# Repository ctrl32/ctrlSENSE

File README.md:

# ctrlSENSE

Open-source IoT temperature sensors – firmware, hardware and server in one repository.

## Repository layout

| Directory | Content | License |
|---|---|---|
| [`firmware/`](firmware/) | Sensor firmware (ESP32, PlatformIO) | GPL-3.0-or-later |
| [`hardware/`](hardware/) | PCB (KiCad) and enclosure (FreeCAD) | CERN-OHL-S-2.0 |
| [`server/`](server/) | Backend and dashboard | AGPL-3.0-or-later |
| [`docs/`](docs/) | Documentation | CC-BY-SA-4.0 |

## Getting started

### Firmware

```bash
cd firmware
pio run                 # build
pio run -t upload       # flash
pio device monitor      # serial monitor
```

Requires [PlatformIO](https://platformio.org/).

### Hardware

Open `hardware/pcb/` in [KiCad](https://www.kicad.org/) 9 and `hardware/enclosure/` in [FreeCAD](https://www.freecad.org/) 1.0 or newer.

## Contributing

Contributions are welcome – see [CONTRIBUTING.md](CONTRIBUTING.md).
Security issues: see [SECURITY.md](SECURITY.md).

## License

ctrlSENSE uses different licenses for different parts of the project – see [LICENSE](LICENSE).
All parts are under strong copyleft licenses: if you distribute modified versions
(or, for the server, run them as a network service), you must publish the
source under the same license.
The ctrlSENSE name and logo are covered by [TRADEMARKS.md](TRADEMARKS.md).

© 2026 ctrl32

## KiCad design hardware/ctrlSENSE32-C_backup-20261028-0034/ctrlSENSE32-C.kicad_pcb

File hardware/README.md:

# ctrlSENSE hardware

| Directory | Content | Tool |
|---|---|---|
| [`pcb/`](pcb/) | Schematic and PCB | KiCad 9 |
| [`enclosure/`](enclosure/) | Enclosure | FreeCAD 1.0+ |

Manufacturing files (Gerber, drill, BOM, pick-and-place) are attached to
[releases](https://github.com/ctrl32/ctrlSENSE/releases) and are not stored in
the repository.

Licensed under [CERN-OHL-S-2.0](../LICENSES/CERN-OHL-S-2.0.txt).
If you distribute a modified design, you must publish its source under the
same license.

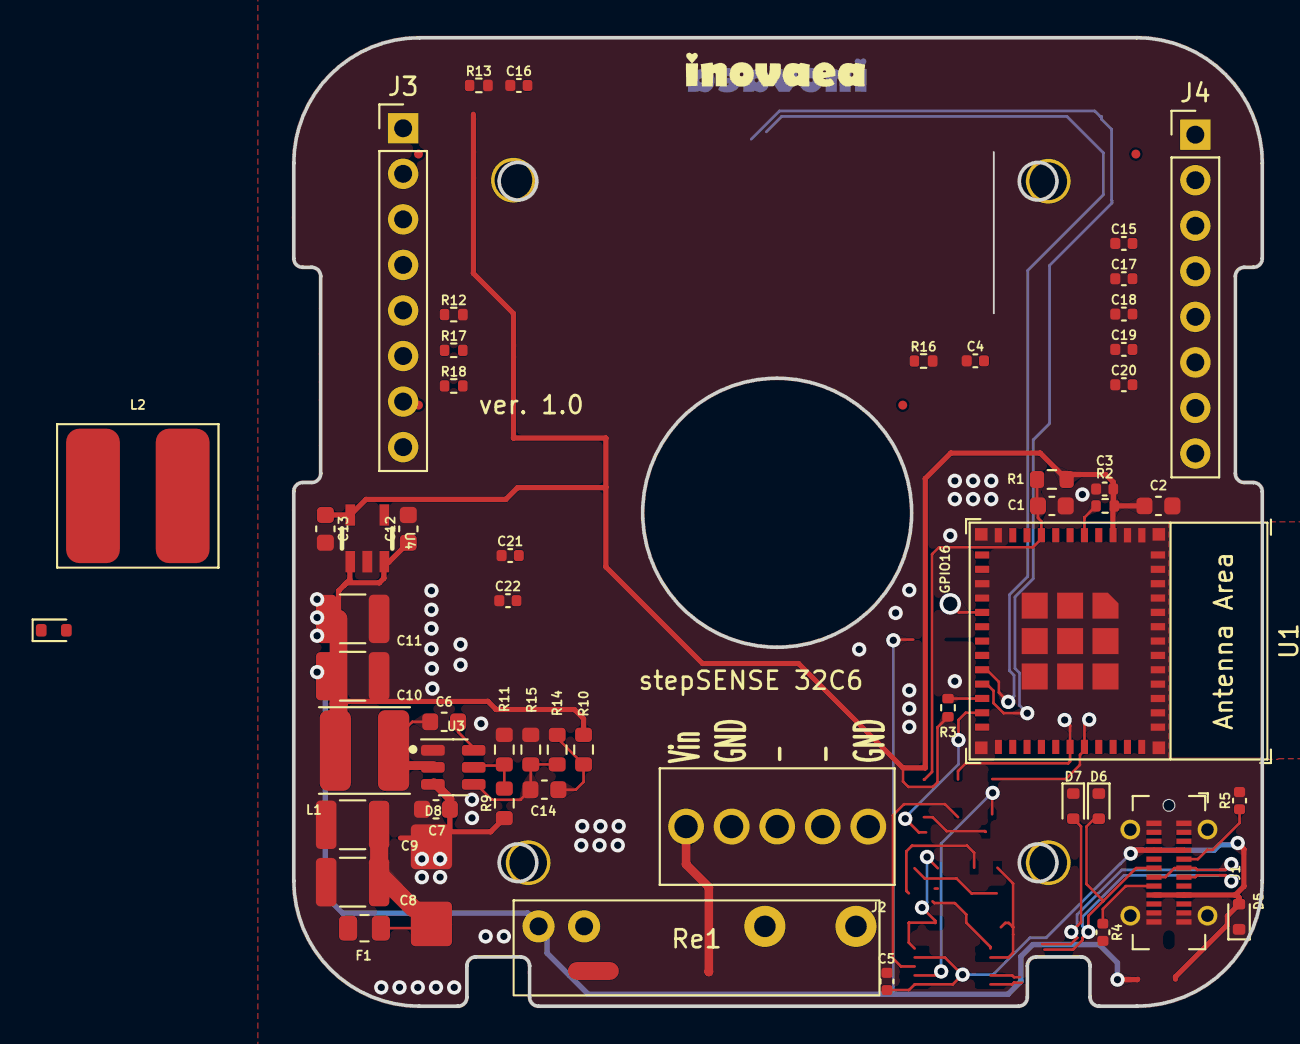
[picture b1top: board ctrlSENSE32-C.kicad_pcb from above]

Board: 4 copper layers, 54.0 x 54.0 mm, 57 parts (0 on the bottom side), 23 nets.

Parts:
C1: 1uF; C_0603
C2, C12, C13: 22uF; C_0603
C3, C4, C5, C15, C16: 100nF; C_0402
C6, C7: 100n; C_0603
C8, C9: 10uF; C_1210
C10, C11: 22uF; C_1210
C14: 75p; C_0603
C17, C18, C19, C20, C21, C22: 1uF; C_0402
D5, D6, D7, D9: LESD5D5.0CT1G; SOD-523
D8: SMBJ30A; SMB
F1: ASMD0805-050-24V; R_0805
FID1, FID2, FID3, FID4: Fiducial; Fiducial_0.5mm_Mask1mm
J1: USB_C_Receptacle_USB2.0; WE_632722110112
J2: Screw_Terminal_01x05; WE_691210910005
J3, J4: PINHD_1x8_Male; PinHeader_1x08_P2.54mm_Vertical
L1: 15uH; WE-PD2_4532
L2: 10uH; WE-PD2_7850_2
R1: 10k; R_0603
R2, R3: 33k; R_0402
R4, R5: 5.1kΩ; R_0402
R9: 510k; R_0603
R10: 49.9; R_0603
R11: 105k; R_0603
R12, R13: 10k; R_0402
R14: 100k; R_0603
R15: 13.3k; R_0603
R16: Rx; R_0402
R17, R18: 4.7; R_0402
Re1: APAN3103; APAN30xx
U1: ESP32-C3-MINI-1
U3: TPS54202DDCR; SOT-23-6
U4: SY8089AAAC; SOT-23-5

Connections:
+3.3V: C2.2, C3.2, C4.2, C15.2, C16.2, C18.2, C20.2, C21.2, C22.2, J4.1, R1.2, R2.1, R3.1, R17.1, R18.1, U1.3 (3V3)
+5V: C10.1, C11.1, J3.1, L1.2, R10.1
+5V_USB: C5.2, D5.2 (A2), J1.A4 (VBUS), J1.A9 (VBUS), J1.B4 (VBUS), J1.B9 (VBUS)
+24V: F1.1, J2.5
/CC1: J1.A5 (CC1), R5.1
/CC2: J1.B5 (CC2), R4.1
/D_N: D6.2 (A2), J1.A7 (D-), J1.B7 (D-)
/D_P: D7.2 (A2), J1.A6 (D+), J1.B6 (D+)
/ESP_EN: C1.2, R1.1, U1.8 (EN/CHIP_PU)
/SCL: R12.1, U1.20 (GPIO6)
/SDA: R13.1, U1.21 (GPIO7)
/SW: C6.2, L1.1, U3.2 (SW)
GND: C1.1, C2.1, C3.1, C4.1, C5.1, C7.2, C8.2, C9.2, C10.2, C11.2, C12.2, C13.2, C15.1, C16.1, C17.1, C18.1, C19.1, C20.1, C21.1, C22.1, D5.1 (A1), D6.1 (A1), D7.1 (A1), D8.2 (A2), J1.A1 (GND), J1.A12 (GND), J1.B1 (GND), J1.B12 (GND), J1.S1 (SHIELD), J2.1, J2.4, J4.6, R4.2, R5.2, R11.2, R12.2, R13.2, R15.2, R16.2, U1.1 (GND), U1.2 (GND), U1.11 (GND), U1.14 (GND), U1.36 (GND), U1.37 (GND), U1.38 (GND), U1.39 (GND), U1.40 (GND), U1.41 (GND), U1.42 (GND), U1.43 (GND), U1.44 (GND), U1.45 (GND), U1.46 (GND), U1.47 (GND), U1.48 (GND), U1.49 (GND), U1.50 (GND), U1.51 (GND), U1.52 (GND), U1.53 (GND), U3.1 (GND), U4.2 (GND)
unnamed: C14.2, R10.2, R14.1
unnamed: C7.1, C8.1, C9.1, D8.1 (A1), F1.2, R9.1, U3.3 (Vin)
unnamed: C12.1, U4.1 (EN), U4.4 (IN)
unnamed: R2.2, U1.5 (GPIO2/ADC1_CH2)
unnamed: R3.2, U1.22 (GPIO8)
unnamed: C6.1, U3.6 (BOOT)
unnamed: R9.2, R11.1, U3.5 (EN)
unnamed: C14.1, R14.2, R15.1, U3.4 (FB)
unnamed: C17.2, R17.2
unnamed: C19.2, R18.2
